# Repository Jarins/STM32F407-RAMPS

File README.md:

# RAMPS for STM32F407ZET6 and STM32F407ZGT6 development board Black edition from China

for example from aliexpress [e.g. here](https://www.aliexpress.com/wholesale?catId=0&initiative_id=SB_20200509043338&SearchText=stm32f407Zet6+development+board)
with pins directly compatible with original TFT display 3.2 inch 320x240 with Touch panel  [e.g. here](https://www.aliexpress.com/wholesale?catId=0&initiative_id=SB_20200509115015&origin=y&SearchText=3.2+TFT+for+STM32F407VET6)

## __Work-in-progress__

The first usable version of the PCB.

Features of the RAMPS board:
-----
  + up to 5x replaceable stepper motor drivers 
  + up to 4 thermistors or 4 thermocouples for temperature control
  + 3 power heaters (*1 bed and up to 2 extruder heaters*) with PWM power control up to 50A (*180A 60V MOSFET params, 30A without cooling, llimited by the used connector and the width of the cooper on the PCB see bellow*)
  + The heaters and motor controllers are guided by a wire width of 2.5 mm on both sides of the PCB = 5 mm = 10 A current when heating the wire by max. 15 ° C
  + replaceable fuse for all three heaters
  + 4 high power PWM connectors with selectable voltage for fans, LEDs or DC motors
    - 5V up to 3A in total for all outputs
    - 12V up to 3A in total for all outputs
    - VIN(*24V*) up to 20A each individually (*limited by the used connector and the width of the cooper on the PCB*)
  + 2 PWM Servos outputs - powered is optionally 3.3V or 5V(*in the future it will probably be canceled, because 3.3v is formed by a linear stabilizer AMS111 directly on the CPU board and the consumption of 2 servos can cause considerable overheating of the component*)
  + 6 end stops 
  + micro-sd card support with SDIO for fast file transfer
  + ports - serial, USB, I2C and 2x SPI
  + FSMC 16bit TFT port with SPI touch for [high resolution graphics display](https://www.aliexpress.com/wholesale?catId=0&initiative_id=SB_20200509115015&origin=y&SearchText=3.2+TFT+for+STM32F407VET6)  or RAMPS standard 2 flat cable LCD screen support(128x60 graphics with push-button encoder and SD Card)
  + Input voltage: 12-24V
  + Super low cost (*$0.85/piece*) 2 x DC-DC Buck regulators [Mini DC-DC 4.5-24V To 5V and 12V 3A](https://www.aliexpress.com/wholesale?catId=0&initiative_id=SB_20200509121836&origin=y&SearchText=Mini+DC-DC+12-24V+To+5V+3A+) using  MP2315 chip from MPS, which are absolutely cold during operation even at full load 3A.
  + On the STM32F407 board used 16Mbit(2MB) flash for EEPROM emulation.
  + Marlin 2.05 firmware support FSMC paralel 16 bit TFT display with Touch. 
  
  + Low cost and small board dimensions 110 x 84mm (At [JLCPCB](https://jlcpcb.com/) only $7 for 5 pieces + $7 postage = $2.8 / piece)

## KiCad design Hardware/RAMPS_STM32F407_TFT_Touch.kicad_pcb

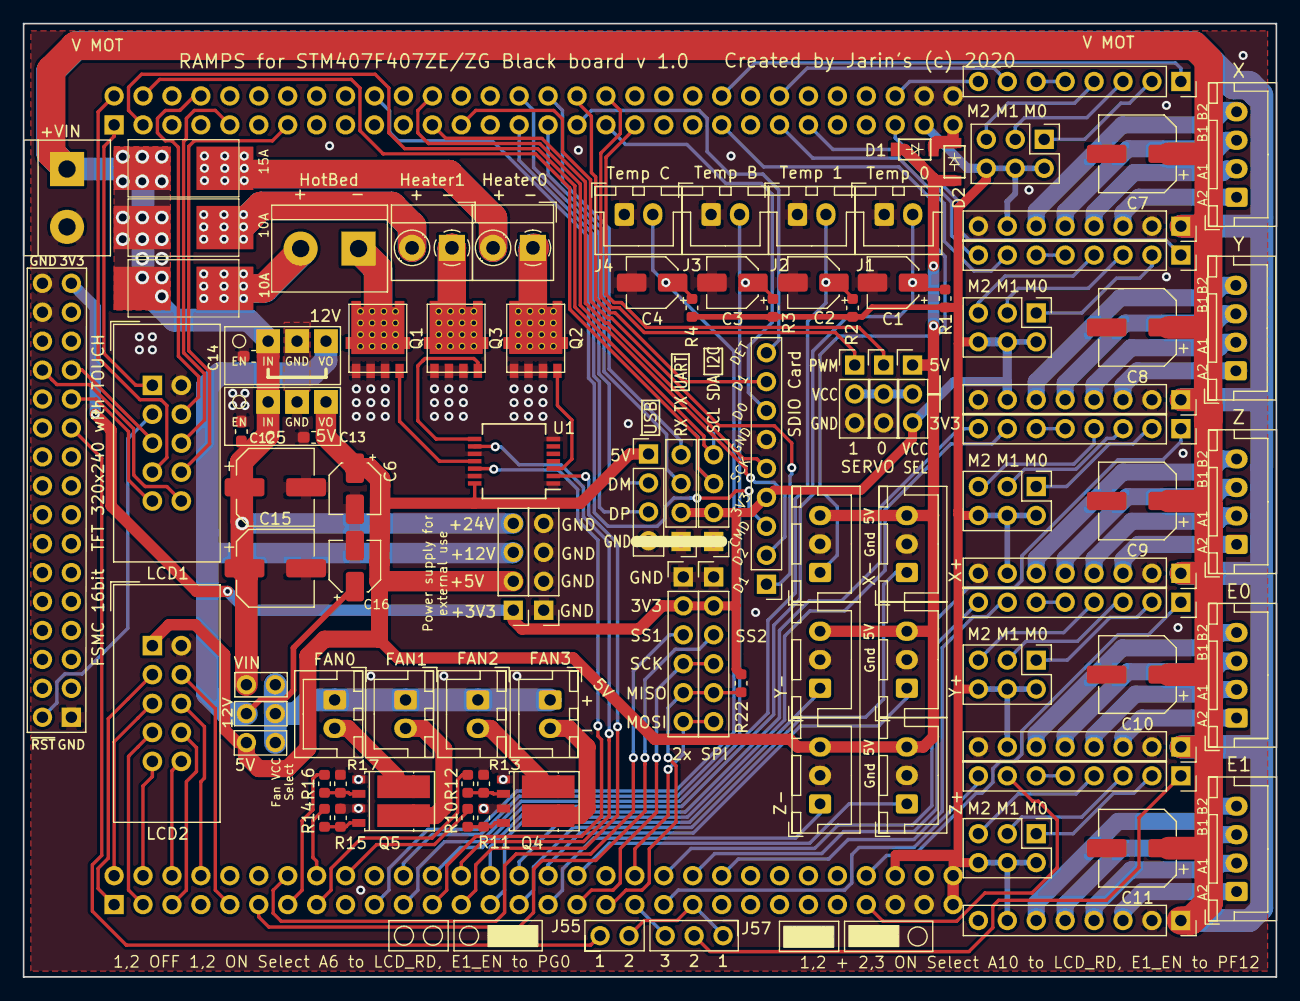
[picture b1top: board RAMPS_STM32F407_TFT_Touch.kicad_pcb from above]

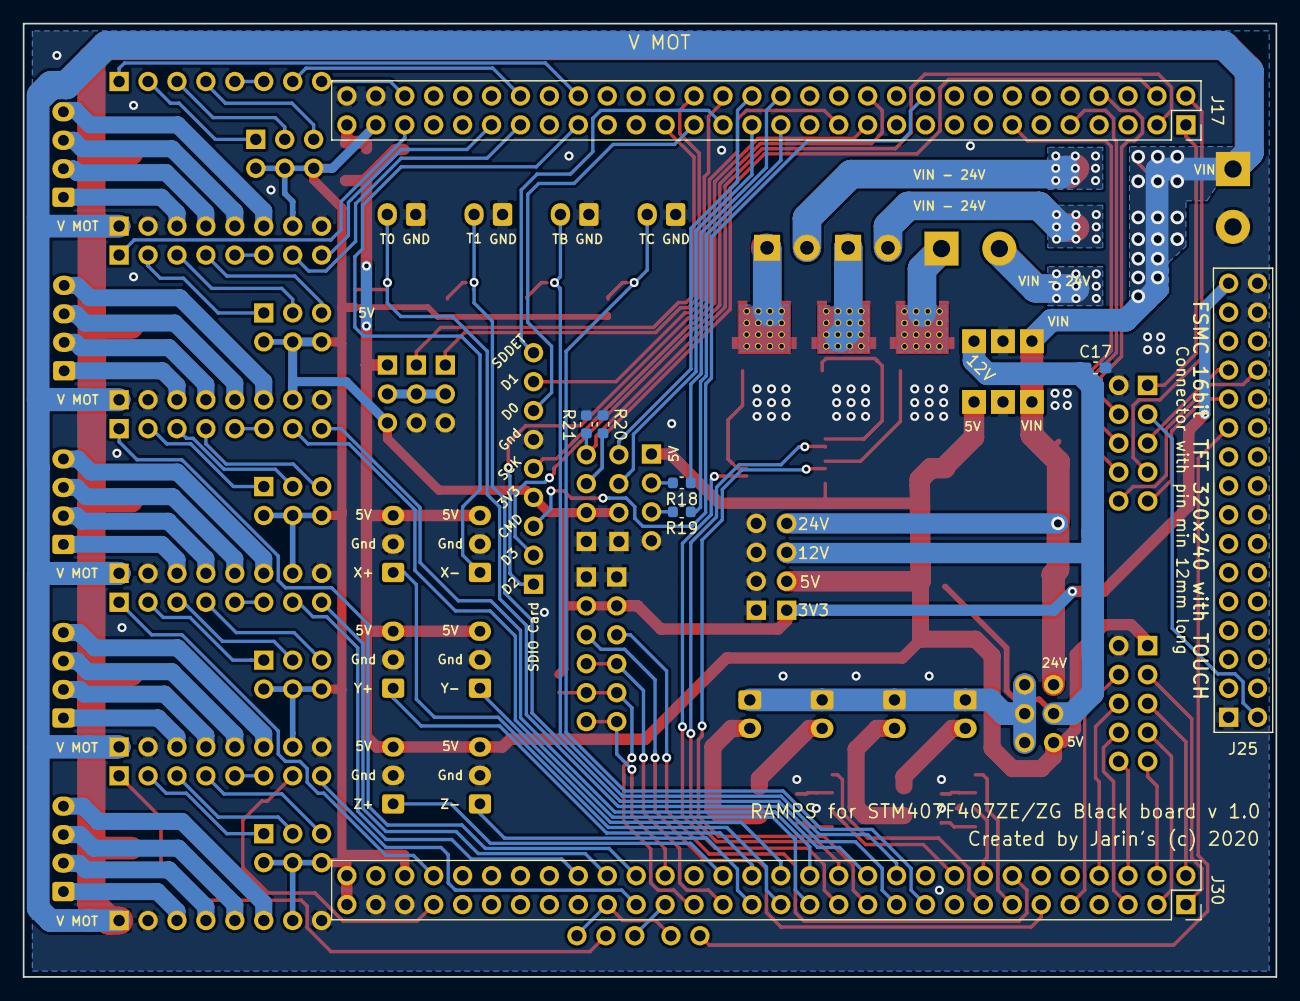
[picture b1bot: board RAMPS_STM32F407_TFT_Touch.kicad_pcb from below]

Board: 2 copper layers, 110.0 x 83.7 mm, 104 parts (8 on the bottom side), 139 nets.

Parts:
C1, C2, C3, C4: 10uF 16V; CP_Elec_4x5.3
C5, C15: 100uF; CP_Elec_6.3x5.8
C6, C16: 10uF; CP_Elec_4x5.4
C7, C8, C9, C10, C11: 100uF 35V; CP_Elec_6.3x5.8
C12, C13, C14, C17: 100n; C_0603_1608Metric_Pad1.05x0.95mm_HandSolder
D1, D2: MBR130LSFT1G; D_SOD-123
F1: 15A; 2410_FuseFolder
F2, F3: 10A; 2410_FuseFolder
J1: TEMP_0; JST_XH_B2B-XH-A_1x02_P2.50mm_Vertical
J2: TEMP_1; JST_XH_B2B-XH-A_1x02_P2.50mm_Vertical
J3: TEMP_B; JST_XH_B2B-XH-A_1x02_P2.50mm_Vertical
J4: TEMP_C; JST_XH_B2B-XH-A_1x02_P2.50mm_Vertical
J5: -VIN+; TerminalBlock_Amphenol-2_P5.08mm
J6: HEATER_B; TerminalBlock_Amphenol-2_P5.08mm
J7: HEATER_0; TerminalBlock_MetzConnect_Type059_RT06302HBWC_1x02_P3.50mm_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
J8: HEATER_1; TerminalBlock_MetzConnect_Type059_RT06302HBWC_1x02_P3.50mm_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
J9: FAN3; JST_XH_B2B-XH-A_1x02_P2.50mm_Vertical
J10: FAN2; JST_XH_B2B-XH-A_1x02_P2.50mm_Vertical
J11: FAN1; JST_XH_B2B-XH-A_1x02_P2.50mm_Vertical
J12: X_logic; PinSocket_1x08_P2.54mm_Vertical
J13, J22, J26, J29, J32: Microsteps; PinHeader_2x03_P2.54mm_Vertical
J14: X-; JST_XH_B3B-XH-A_1x03_P2.50mm_Vertical
J15: Y-; JST_XH_B3B-XH-A_1x03_P2.50mm_Vertical
J16: Z-; JST_XH_B3B-XH-A_1x03_P2.50mm_Vertical
J17: Left; PinSocket_2x30_P2.54mm_Vertical
J18: Y_logic; PinSocket_1x08_P2.54mm_Vertical
J19: X+; JST_XH_B3B-XH-A_1x03_P2.50mm_Vertical
J20: Y+; JST_XH_B3B-XH-A_1x03_P2.50mm_Vertical
J21: Z+; JST_XH_B3B-XH-A_1x03_P2.50mm_Vertical
J23: LCD2; IDC-Header_2x05_P2.54mm_Vertical
J24: Z_logic; PinSocket_1x08_P2.54mm_Vertical
J25: TFT_FSCM; PinSocket_2x16_P2.54mm_Vertical_14mmPinLong
J27: LCD1; IDC-Header_2x05_P2.54mm_Vertical
J28: E0_logic; PinSocket_1x08_P2.54mm_Vertical
J30: Right; PinSocket_2x30_P2.54mm_Vertical
J31: E1_logic; PinSocket_1x08_P2.54mm_Vertical
J33: X_motor; PinSocket_1x08_P2.54mm_Vertical
J34: Y_motor; PinSocket_1x08_P2.54mm_Vertical
J35: Z_motor; PinSocket_1x08_P2.54mm_Vertical
J36: E0_motor; PinSocket_1x08_P2.54mm_Vertical
J37: E1_motor; PinSocket_1x08_P2.54mm_Vertical
J38: X; JST_XH_B4B-XH-A_1x04_P2.50mm_Vertical
J39: Y; JST_XH_B4B-XH-A_1x04_P2.50mm_Vertical
J40: Z; JST_XH_B4B-XH-A_1x04_P2.50mm_Vertical
J41: E0; JST_XH_B4B-XH-A_1x04_P2.50mm_Vertical
J42: E1; JST_XH_B4B-XH-A_1x04_P2.50mm_Vertical
J43: FAN0; JST_XH_B2B-XH-A_1x02_P2.50mm_Vertical
J44: COM; PinHeader_1x04_P2.54mm_Vertical
J45: USB; PinHeader_1x04_P2.54mm_Vertical
J46, J54: Power; PinHeader_1x04_P2.54mm_Vertical
J47: I2C; PinHeader_1x04_P2.54mm_Vertical
J48, J49: SPI; PinHeader_1x06_P2.54mm_Vertical
J50: SDIO; PinHeader_1x09_P2.54mm_Vertical
J51, J52: Servo; PinHeader_1x03_P2.54mm_Vertical
J53: PowerSelect; PinHeader_1x03_P2.54mm_Vertical
J55: Conn_01x02; PinHeader_1x02_P2.54mm_Vertical
J56: Power; PinHeader_2x03_P2.54mm_Vertical
J57: LCD RS Select; PinHeader_1x03_P2.54mm_Vertical
Q1, Q2, Q3: NTMFS5C628; NTMFS5C628NL
Q4, Q5: BUK9K17-60E; LFPAK56D
R1, R2, R3, R4, R20, R21, R22: 4K7; R_0603_1608Metric
R10, R12, R14, R16: 10; R_0603_1608Metric
R11, R13, R15, R17: 10K; R_0603_1608Metric
R18, R19: 22R; R_0603_1608Metric
U1: 74LVC125; SSOP-14_5.3x6.2mm_P0.65mm
X01, X02: MP2315

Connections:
+3V3: J13.2, J13.4, J13.6, J17.57, J22.2, J22.4, J22.6, J25.31, J26.2, J26.4, J26.6, J29.2, J29.4, J29.6, J30.56, J30.59, J30.60, J32.2, J32.4, J32.6, J33.7, J34.7, J35.7, J36.7, J37.7, J44.2, J47.2, J48.2, J49.2, J50.4, J53.3, J54.1, R1.1, R2.1, R3.1, R4.1, R22.2
+5V: C6.1, C13.1, D1.2, D2.2, J14.3, J15.3, J16.3, J19.3, J20.3, J21.3, J27.1, J45.1, J53.1, J54.2, J56.5, U1.14, X01.3
+12V: C16.1, C17.1, J54.3, J56.3, X02.3
+24V: C5.1, C7.1, C8.1, C9.1, C10.1, C11.1, C12.1, C14.1, C15.1, F1.1, F2.1, F3.1, J5.1, J33.1, J34.1, J35.1, J36.1, J37.1, J54.4, J56.1, X01.1, X02.1
/ABORT: J17.1, J23.1
/BEEPER: J27.10, J30.6
/E0_DIR: J28.8, J30.42
/E0_EN: J28.1, J30.54
/E0_STEP: J28.7, J30.44
/E1_DIR: J30.39, J31.8
/E1_EN: J31.1, J57.2
/E1_STEP: J30.53, J31.7
/EN1: J17.13, J23.8
/EN2: J17.9, J23.6
/ENC: J27.9, J30.4
/FAN0: J30.13, R16.2
/FAN1: J30.16, R14.2
/FAN2: J30.15, R12.2
/FAN3: J30.18, R10.2
/HEATER_0: J30.25, U1.2
/HEATER_1: J30.26, U1.9
/HEATER_B: J30.23, U1.12
/LCD4: J27.6, J30.8
/LCD5: J27.5, J30.2
/LCD6: J27.4, J30.9
/LCD7: J27.3, J30.1
/LCDE: J27.8, J30.5
/LCDRS: J27.7, J30.3
/MISO: J30.35, J48.5, J49.5, R22.1
/MOSI: J30.38, J48.6, J49.6
/RX: J17.31, J44.3
/SCK: J30.33, J48.4, J49.4
/SCL: J17.4, J47.3, R20.1
/SDA: J17.3, J47.4, R21.2
/SDDET: J17.8, J23.4
/SDIO_CMD: J17.20, J50.3
/SDIO_D0: J17.35, J50.7
/SDIO_D1: J17.34, J50.8
/SDIO_D2: J17.25, J50.1
/SDIO_D3: J17.24, J50.2
/SDIO_DET: J17.33, J50.9
/SDIO_SCK: J17.23, J50.5
/SDSS: J17.2, J23.7
/SERVO0: J17.37, J52.1
/SERVO1: J17.36, J51.1
/SS1: J30.14, J48.3
/SS2: J30.11, J49.3
/TEMP_0: C1.1, J1.2, J30.24, R1.2
/TEMP_1: C2.1, J2.2, J30.21, R2.2
/TEMP_B: C3.1, J3.2, J30.22, R3.2
/TEMP_C: C4.1, J4.2, J30.19, R4.2
/TX: J17.32, J44.4
/T_CLK: J23.9, J25.23
/T_MISO: J23.10, J25.26
/T_MOSI: J23.5, J25.25
/USB_DM: J17.30, R18.1
/USB_DP: J17.29, R19.1
/X_DIR: J12.8, J17.56
/X_EN: J12.1, J17.44
/X_MAX: J19.1, J30.29
/X_MIN: J14.1, J17.43
/X_STEP: J12.7, J17.48
/Y_DIR: J17.49, J18.8
/Y_EN: J17.55, J18.1
/Y_MAX: J20.1, J30.32
/Y_MIN: J15.1, J30.30
/Y_STEP: J17.47, J18.7
/Z_DIR: J24.8, J30.28
/Z_EN: J24.1, J30.40
/Z_MAX: J21.1, J30.34
/Z_MIN: J16.1, J30.31
/Z_STEP: J24.7, J30.27
/~RESET: J23.3, J25.2
GND: C1.2, C2.2, C3.2, C4.2, C5.2, C6.2, C7.2, C8.2, C9.2, C10.2, C11.2, C12.2, C13.2, C14.2, C15.2, C16.2, C17.2, J1.1, J2.1, J3.1, J4.1, J5.2, J14.2, J15.2, J16.2, J17.58, J17.60, J19.2, J20.2, J21.2, J23.2, J25.1, J25.30, J25.32, J27.2, J30.55, J30.57, J33.2, J33.8, J34.2, J34.8, J35.2, J35.8, J36.2, J36.8, J37.2, J37.8, J44.1, J45.4, J46.1, J46.2, J46.3, J46.4, J47.1, J48.1, J49.1, J50.6, J51.3, J52.3, Q1.3, Q2.3, Q3.3, Q4.1, Q4.3, Q5.1, Q5.3, R11.1, R13.1, R15.1, R17.1, R20.2, R21.1, U1.1, U1.7, U1.10, U1.13, X01.2, X02.2
unnamed: D1.1, D2.1, J17.59
unnamed: F1.2, J7.2
unnamed: F2.2, J8.2
unnamed: F3.2, J6.2
unnamed: J6.1, Q1.2
unnamed: J7.1, Q2.2
unnamed: J8.1, Q3.2
unnamed: J9.2, Q4.5
unnamed: J9.1, J10.1, J11.1, J43.1, J56.2, J56.4, J56.6
unnamed: J10.2, Q4.6
unnamed: J11.2, Q5.5
unnamed: J12.2, J13.1
unnamed: J12.3, J13.3
unnamed: J12.4, J13.5
unnamed: J12.5, J12.6
unnamed: J18.2, J22.1
unnamed: J18.3, J22.3
unnamed: J18.4, J22.5
unnamed: J18.5, J18.6
unnamed: J24.2, J26.1
unnamed: J24.3, J26.3
unnamed: J24.4, J26.5
unnamed: J24.5, J24.6
unnamed: J25.21, J55.1
unnamed: J28.2, J29.1
unnamed: J28.3, J29.3
unnamed: J28.4, J29.5
unnamed: J28.5, J28.6
unnamed: J30.37, J57.3
unnamed: J30.41, J55.2, J57.1
unnamed: J31.2, J32.1
unnamed: J31.3, J32.3
unnamed: J31.4, J32.5
unnamed: J31.5, J31.6
unnamed: J33.3, J38.1
unnamed: J33.4, J38.2
unnamed: J33.5, J38.3
unnamed: J33.6, J38.4
unnamed: J34.3, J39.1
unnamed: J34.4, J39.2
unnamed: J34.5, J39.3
unnamed: J34.6, J39.4
unnamed: J35.3, J40.1
unnamed: J35.4, J40.2
unnamed: J35.5, J40.3
unnamed: J35.6, J40.4
unnamed: J36.3, J41.1
unnamed: J36.4, J41.2
unnamed: J36.5, J41.3
unnamed: J36.6, J41.4
unnamed: J37.3, J42.1
unnamed: J37.4, J42.2
unnamed: J37.5, J42.3
unnamed: J37.6, J42.4
unnamed: J43.2, Q5.6
unnamed: J45.2, R18.2
unnamed: J45.3, R19.2
unnamed: J51.2, J52.2, J53.2
unnamed: Q1.1, U1.11
unnamed: Q2.1, U1.3
unnamed: Q3.1, U1.8
unnamed: Q4.2, R12.1, R13.2
unnamed: Q4.4, R10.1, R11.2
unnamed: Q5.2, R16.1, R17.2
unnamed: Q5.4, R14.1, R15.2

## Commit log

2020-05-08 Create Doc
2020-05-09 Create t-txt
2020-05-09 Create Nový textový dokument.txt
    sd
2020-05-09 xxxx
2020-05-09 Added KiCADlibrary and 3Dshapes
2020-05-09 Add Gerber files
2020-05-09 Add datasheet
2020-05-10 Add SMD Fuse datasheet
2020-05-10 Add fuse
2020-05-11 Add Schottky to 5V(usb port protection)
2020-05-11 Schematic PDF
2020-05-30 Correct the placement of the connectors in the correct position
2020-05-30 Repair locations of the connectors in the correct position

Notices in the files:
Hardware/RAMPS_STM32F407_TFT_Touch.kicad_pcb:
Created by Jarin's (c) 2020
